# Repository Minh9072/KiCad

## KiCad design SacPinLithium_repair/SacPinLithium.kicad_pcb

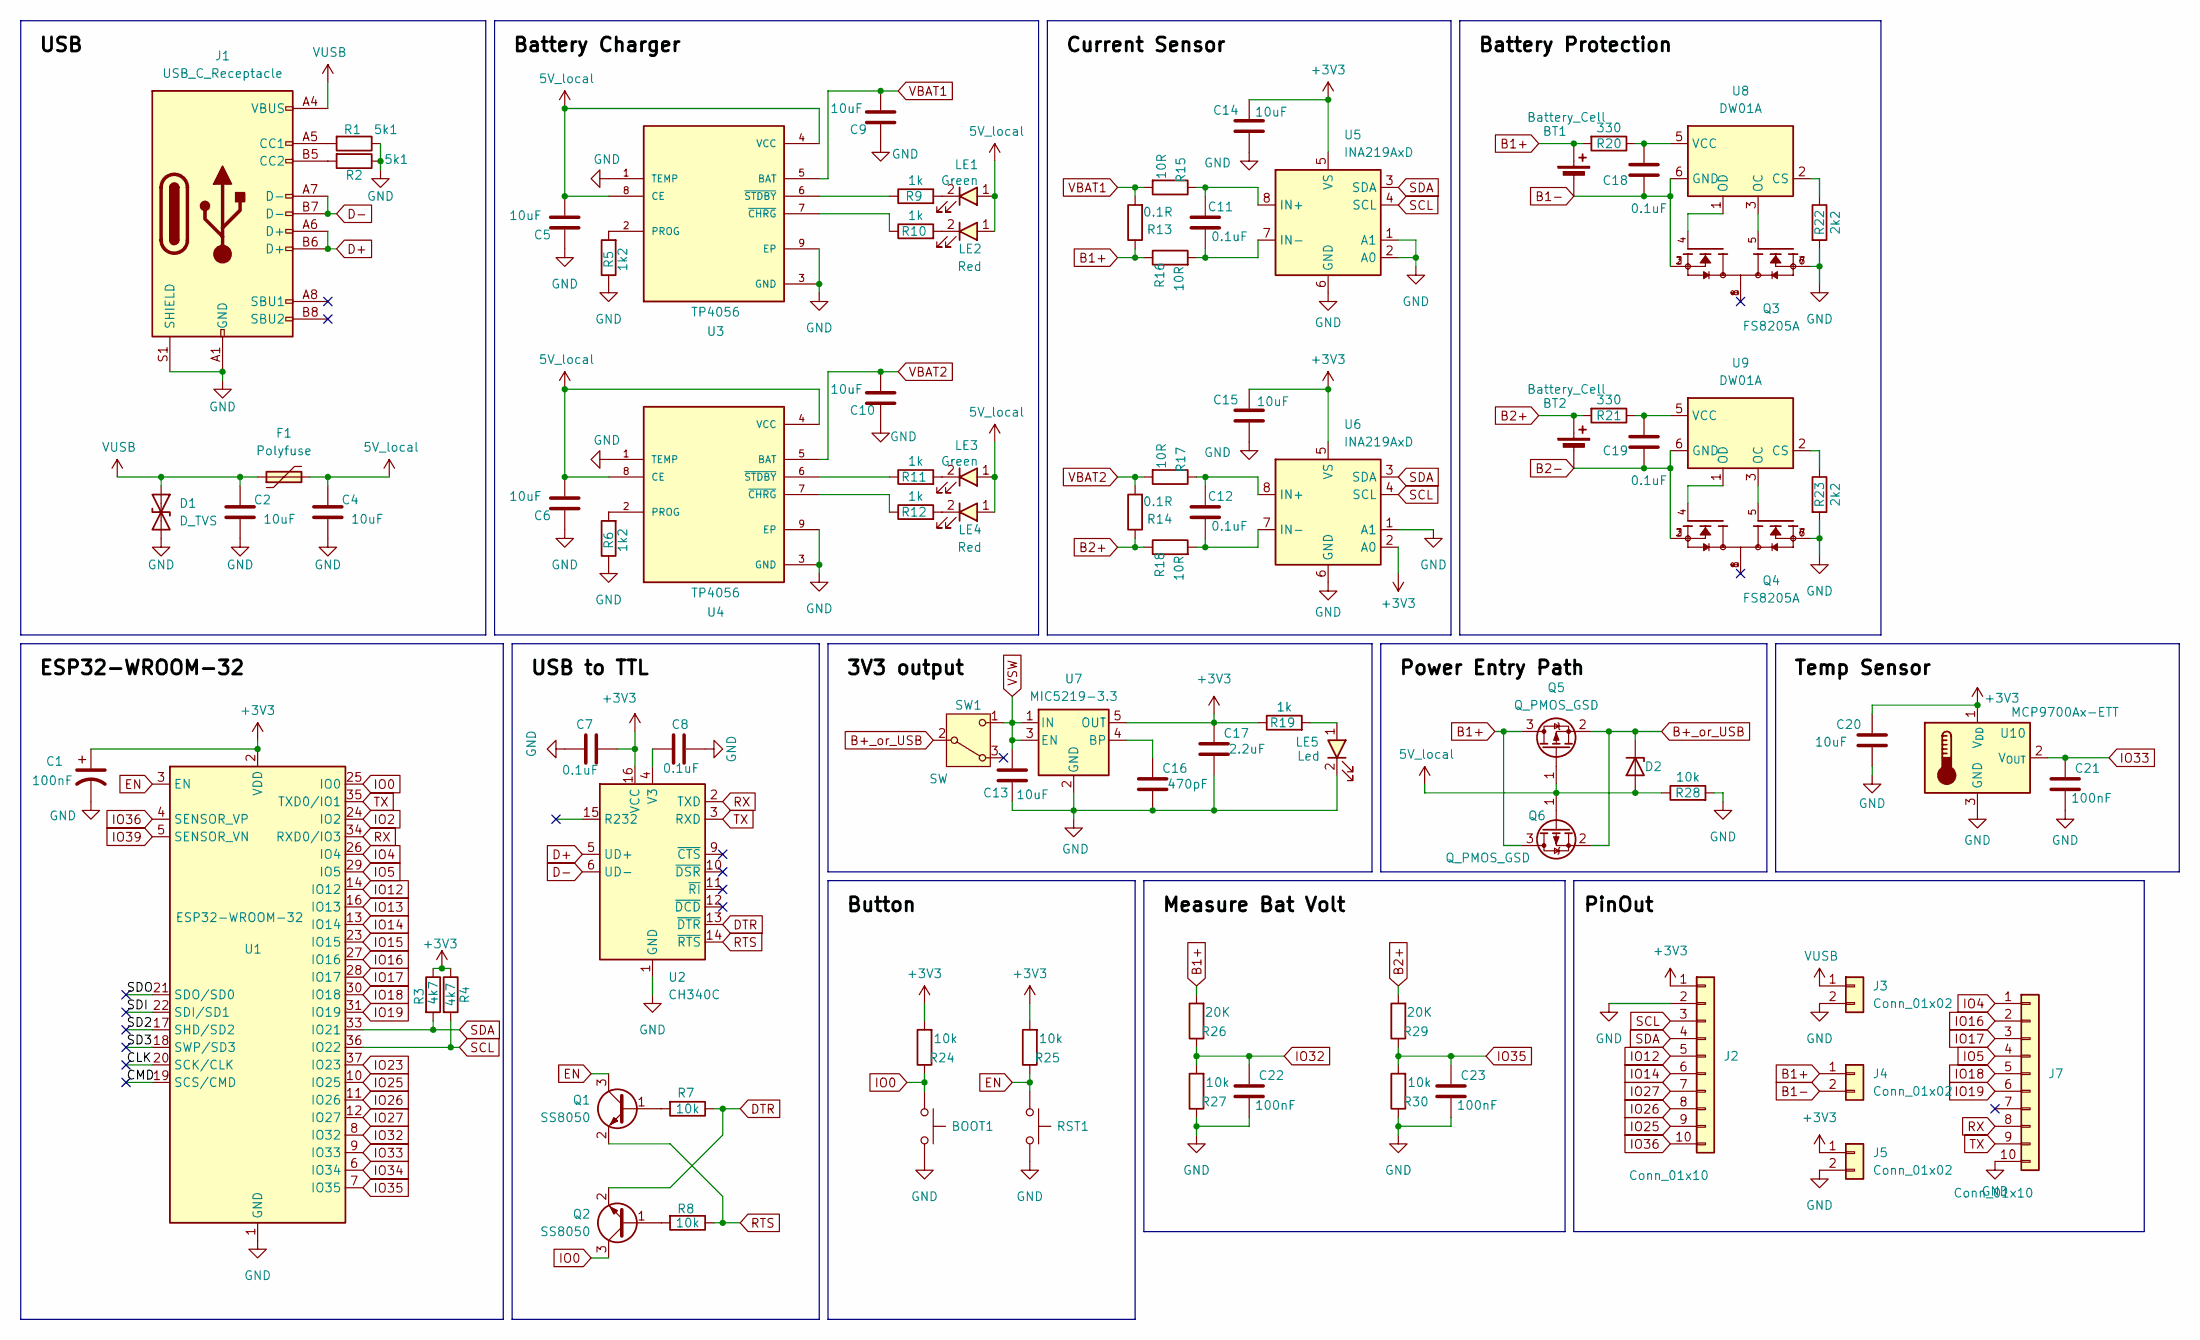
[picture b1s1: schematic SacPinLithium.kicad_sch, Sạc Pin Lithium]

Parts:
BOOT1: SW_Push; SW_Push_SPST_NO_Alps_SKRK
BT1, BT2: Battery_Cell; Minh_BatteryHolder_Keystone_1042_1x18650
C1, C21, C22, C23: 100nF; C_0603
C2, C4, C5, C6, C9, C10, C13, C14, C15, C20: 10uF; C_0603
C7, C8, C11, C12, C18, C19: 0.1uF; C_0603
C16: 470pF; C_0603
C17: 2.2uF; C_0603
D1: D_TVS; Package-Diode-D_SMA
D2: D_SMA
F1: Polyfuse; Fuse_1812_4532Metric
J1: USB_C_Receptacle; USB_C_Receptacle_XKB_U262-16XN-4BVC11
J2, J7: Conn_01x10; PinSocket_1x10_P2.54mm_Vertical
J3, J4, J5: Conn_01x02; PinHeader_1x02_P2.54mm_Vertical
LE1, LE3: Green; L_0603
LE2, LE4: Red; L_0603
LE5: Led; L_0603
Q1, Q2: SS8050; SOT23-3
Q3, Q4: FS8205A; TSSOP-8_4.4x3mm_P0.65mm; PARTREV 1.7
Q5, Q6: Q_PMOS_GSD; SOT23-3
R1, R2: 5k1; R_0805
R3, R4: 4k7; R_0603
R5, R6: 1k2; R_0603
R7, R8, R24, R25, R27, R28, R30: 10k; R_0603
R9, R10, R11, R12, R19: 1k; R_0603
R13, R14: 0.1R; R_2512
R15, R16, R17, R18: 10R; R_0603
R20, R21: 330; R_0603
R22, R23: 2k2; R_0603
R26, R29: 20K; R_0603
RST1: SW_Push; SW_Push_SPST_NO_Alps_SKRK
SW1: SW; SlideSwitch-SS_12F23G4
U1: ESP32-WROOM-32; Minh_ESP32-WROOM-32E
U2: CH340C; SOIC-16_3.9x9.9mm_P1.27mm
U3, U4: TP4056; SOIC-8-1EP_3.9x4.9mm_P1.27mm_EP2.514x3.2mm
U5, U6: INA219AxD; SOIC-8_3.9x4.9mm_P1.27mm
U7: MIC5219-3.3; SOT-23-5
U8, U9: DW01A; SOT-23-6
U10: MCP9700Ax-ETT; SOT23-3

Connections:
5V_local: C4.2, C5.1, C6.1, D2.2 (A), F1.2, LE1.1, LE2.1, LE3.1, LE4.1, Q5.1 (G), Q6.1 (G), R28.1, U3.4 (VCC), U3.8 (CE), U4.4 (VCC), U4.8 (CE); also elsewhere on the board
+3V3: C1.1, C7.1, C14.1, C15.1, C17.1, C20.1, J2.1, J5.1, R3.1, R4.1, R19.1, R24.2, R25.2, U1.2 (VDD), U2.16 (VCC), U5.5 (VS), U6.2 (A0), U6.5 (VS), U7.5 (OUT), U10.1 (V_{DD}); also elsewhere on the board
/CLK: U1.20 (SCK/CLK)
/CMD: U1.19 (SCS/CMD)
/SD2: U1.17 (SHD/SD2)
/SD3: U1.18 (SWP/SD3)
/SDI: U1.22 (SDI/SD1)
/SDO: U1.21 (SDO/SD0)
B1+: BT1.1 (+), J4.1, Q5.3 (D), Q6.3 (D), R13.1, R16.1, R20.2, R26.2; also elsewhere on the board
B1-: BT1.2 (-), C18.2, J4.2, Q3.2, Q3.3, U8.6 (GND); also elsewhere on the board
B2+: BT2.1 (+), R14.1, R18.1, R21.2, R29.2
B2-: BT2.2 (-), C19.2, Q4.2, Q4.3, U9.6 (GND)
B+_or_USB: D2.1 (K), Q5.2 (S), Q6.2 (S), SW1.2 (B)
D+: J1.A6 (D+), J1.B6 (D+), U2.5 (UD+)
D-: J1.A7 (D-), J1.B7 (D-), U2.6 (UD-)
DTR: Q2.2 (E), R7.1, U2.13 (~DTR)
EN: Q1.3 (C), R25.1, RST1.1, U1.3 (EN)
GND: BOOT1.2, C1.2, C2.1, C4.1, C5.2, C6.2, C7.2, C8.2, C9.2, C10.2, C13.2, C14.2, C15.2, C16.2, C17.2, C20.2, C21.2, C22.2, C23.2, D1.2 (A2), J1.A1 (GND), J1.A12 (GND), J1.B1 (GND), J1.B12 (GND), J1.S1 (SHIELD), J2.2, J3.2, J5.2, J7.10, LE5.2, Q3.6, Q3.7, Q4.6, Q4.7, R1.1, R2.1, R5.1, R6.1, R22.2, R23.2, R27.1, R28.2, R30.1, RST1.2, U1.1 (GND), U1.15 (GND), U1.38 (GND), U1.39 (GND), U2.1 (GND), U3.1 (TEMP), U3.3 (GND), U3.9 (EP), U4.1 (TEMP), U4.3 (GND), U4.9 (EP), U5.1 (A1), U5.2 (A0), U5.6 (GND), U6.1 (A1), U6.6 (GND), U7.2 (GND), U10.3 (GND); also elsewhere on the board
IO0: BOOT1.1, Q2.3 (C), R24.1, U1.25 (IO0)
IO2: U1.24 (IO2)
IO4: J7.1, U1.26 (IO4)
IO5: J7.4, U1.29 (IO5)
IO12: J2.5, U1.14 (IO12)
IO13: U1.16 (IO13)
IO14: J2.6, U1.13 (IO14)
IO15: U1.23 (IO15)
IO16: J7.2, U1.27 (IO16)
IO17: J7.3, U1.28 (IO17)
IO18: J7.5, U1.30 (IO18)
IO19: J7.6, U1.31 (IO19)
IO23: U1.37 (IO23)
IO25: J2.9, U1.10 (IO25)
IO26: J2.8, U1.11 (IO26)
IO27: J2.7, U1.12 (IO27)
IO32: C22.1, R26.1, R27.2, U1.8 (IO32)
IO33: C21.1, U1.9 (IO33), U10.2 (V_{OUT})
IO34: U1.6 (IO34)
IO35: C23.1, R29.1, R30.2, U1.7 (IO35)
IO36: J2.10, U1.4 (SENSOR_VP)
IO39: U1.5 (SENSOR_VN)
unnamed: J1.A5 (CC1), R1.2
unnamed: J1.B5 (CC2), R2.2
unnamed 42: LE1.2, R9.2; also elsewhere on the board
unnamed 43: LE2.2, R10.2; also elsewhere on the board
unnamed 44: LE3.2, R11.2; also elsewhere on the board
unnamed 45: LE4.2, R12.2; also elsewhere on the board
unnamed: LE5.1, R19.2
unnamed: Q1.1 (B), R7.2
unnamed: Q2.1 (B), R8.2
unnamed: C8.1, U2.4 (V3)
unnamed: R5.2, U3.2 (PROG)
unnamed: R10.1, U3.7 (~CHRG)
unnamed: R9.1, U3.6 (~STDBY)
unnamed: R6.2, U4.2 (PROG)
unnamed: R12.1, U4.7 (~CHRG)
unnamed: R11.1, U4.6 (~STDBY)
unnamed: C11.1, R15.1, U5.8 (IN+)
unnamed: C11.2, R16.2, U5.7 (IN-)
unnamed: C12.1, R17.1, U6.8 (IN+)
unnamed: C12.2, R18.2, U6.7 (IN-)
unnamed: C16.1, U7.4 (BP)
unnamed: R22.1, U8.2 (CS)
unnamed: Q3.5, U8.3 (OC)
unnamed: Q3.4, U8.1 (OD)
unnamed: C18.1, R20.1, U8.5 (VCC)
unnamed: R23.1, U9.2 (CS)
unnamed: Q4.5, U9.3 (OC)
unnamed: Q4.4, U9.1 (OD)
unnamed: C19.1, R21.1, U9.5 (VCC)
RTS: Q1.2 (E), R8.1, U2.14 (~RTS)
RX: J7.8, U1.34 (RXD0/IO3), U2.2 (TXD)
SCL: J2.3, R4.2, U1.36 (IO22), U5.4 (SCL), U6.4 (SCL)
SDA: J2.4, R3.2, U1.33 (IO21), U5.3 (SDA), U6.3 (SDA)
TX: J7.9, U1.35 (TXD0/IO1), U2.3 (RXD)
VBAT1: C9.1, R13.2, R15.2, U3.5 (BAT)
VBAT2: C10.1, R14.2, R17.2, U4.5 (BAT)
VSW: C13.1, SW1.1 (C), U7.1 (IN), U7.3 (EN)
VUSB: C2.2, D1.1 (A1), F1.1, J1.A4 (VBUS), J1.A9 (VBUS), J1.B4 (VBUS), J1.B9 (VBUS), J3.1; also elsewhere on the board

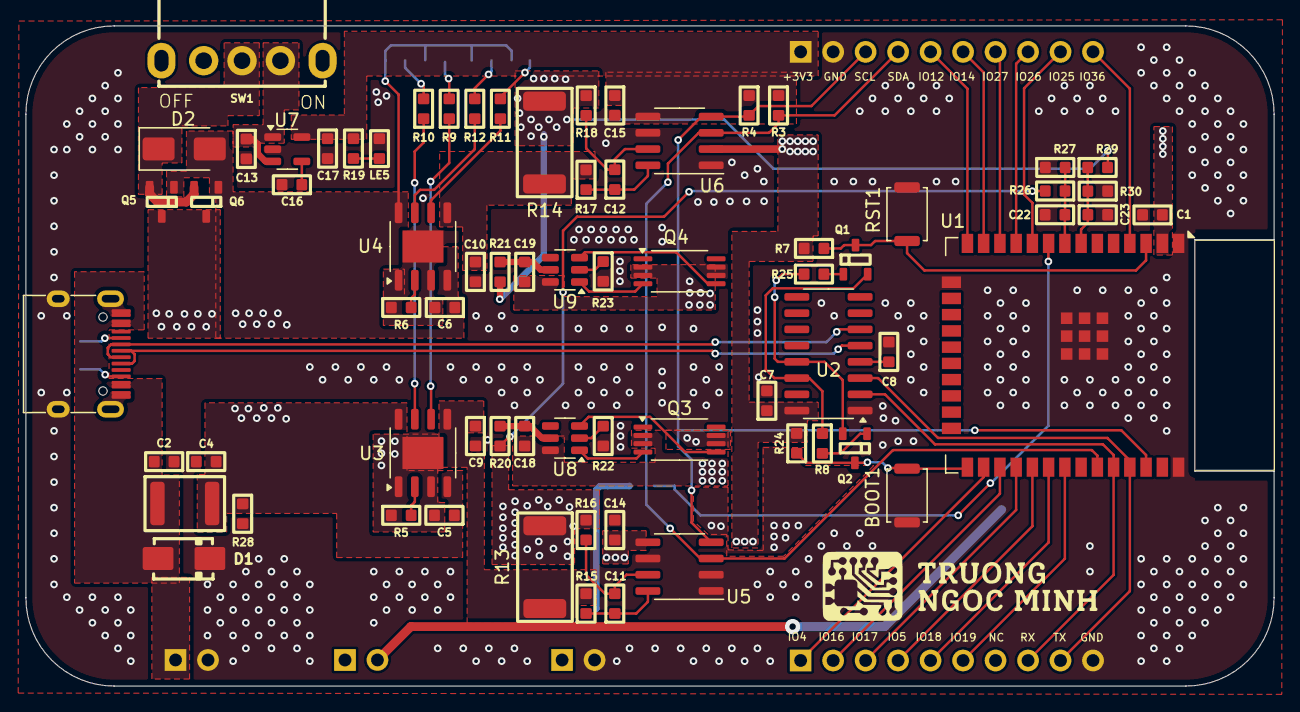
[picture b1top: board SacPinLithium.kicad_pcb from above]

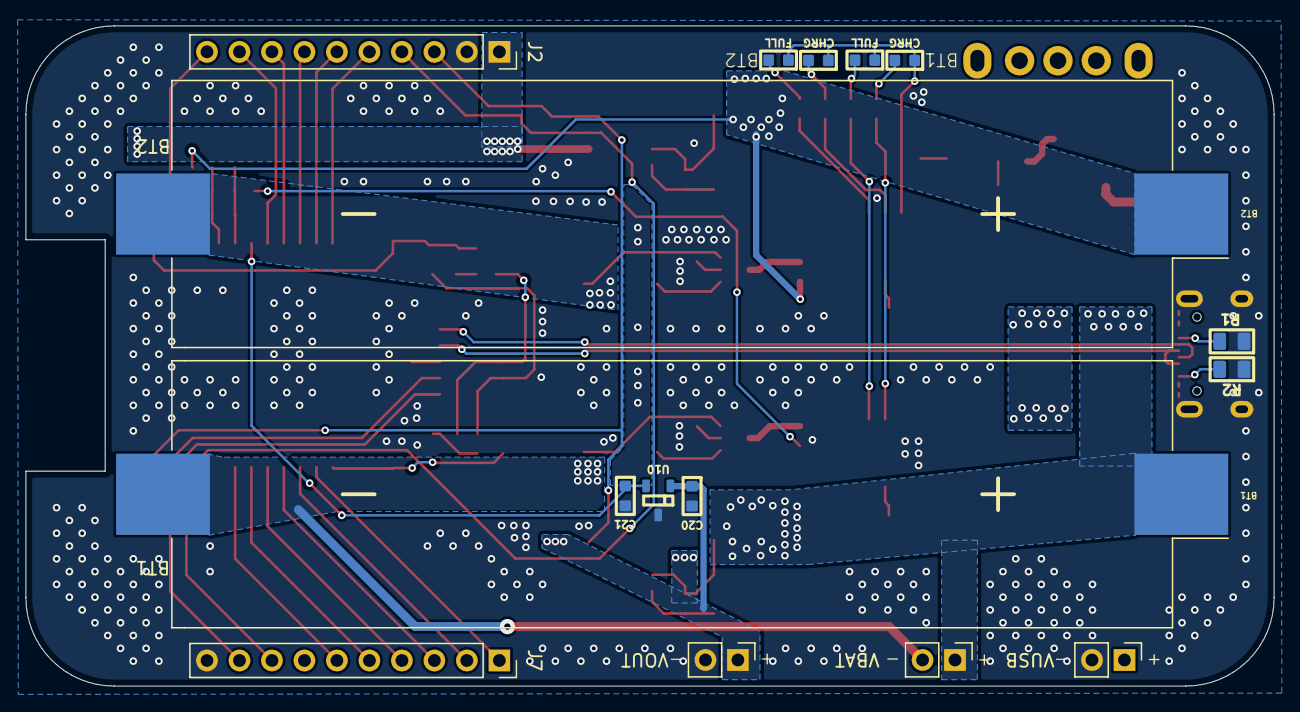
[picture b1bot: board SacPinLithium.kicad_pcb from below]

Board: 2 copper layers, 97.6 x 51.6 mm, 87 parts (16 on the bottom side), 66 nets.

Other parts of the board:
CHRG: Red; L_0603
CHRG#2: Red; L_0603
FULL: Green; L_0603
FULL#2: Green; L_0603
VBAT: Conn_01x02; PinHeader_1x02_P2.54mm_Vertical
VOUT: Conn_01x02; PinHeader_1x02_P2.54mm_Vertical
VUSB: Conn_01x02; PinHeader_1x02_P2.54mm_Vertical

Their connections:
5V_local: CHRG.1, CHRG#2.1, FULL.1, FULL#2.1; also elsewhere on the board
+3V3: VOUT.1; also elsewhere on the board
B1+: VBAT.1; also elsewhere on the board
B1-: VBAT.2; also elsewhere on the board
GND: VOUT.2, VUSB.2; also elsewhere on the board
unnamed 42: FULL.2; also elsewhere on the board
unnamed 43: CHRG#2.2; also elsewhere on the board
unnamed 44: FULL#2.2; also elsewhere on the board
unnamed 45: CHRG.2; also elsewhere on the board
VUSB: VUSB.1; also elsewhere on the board

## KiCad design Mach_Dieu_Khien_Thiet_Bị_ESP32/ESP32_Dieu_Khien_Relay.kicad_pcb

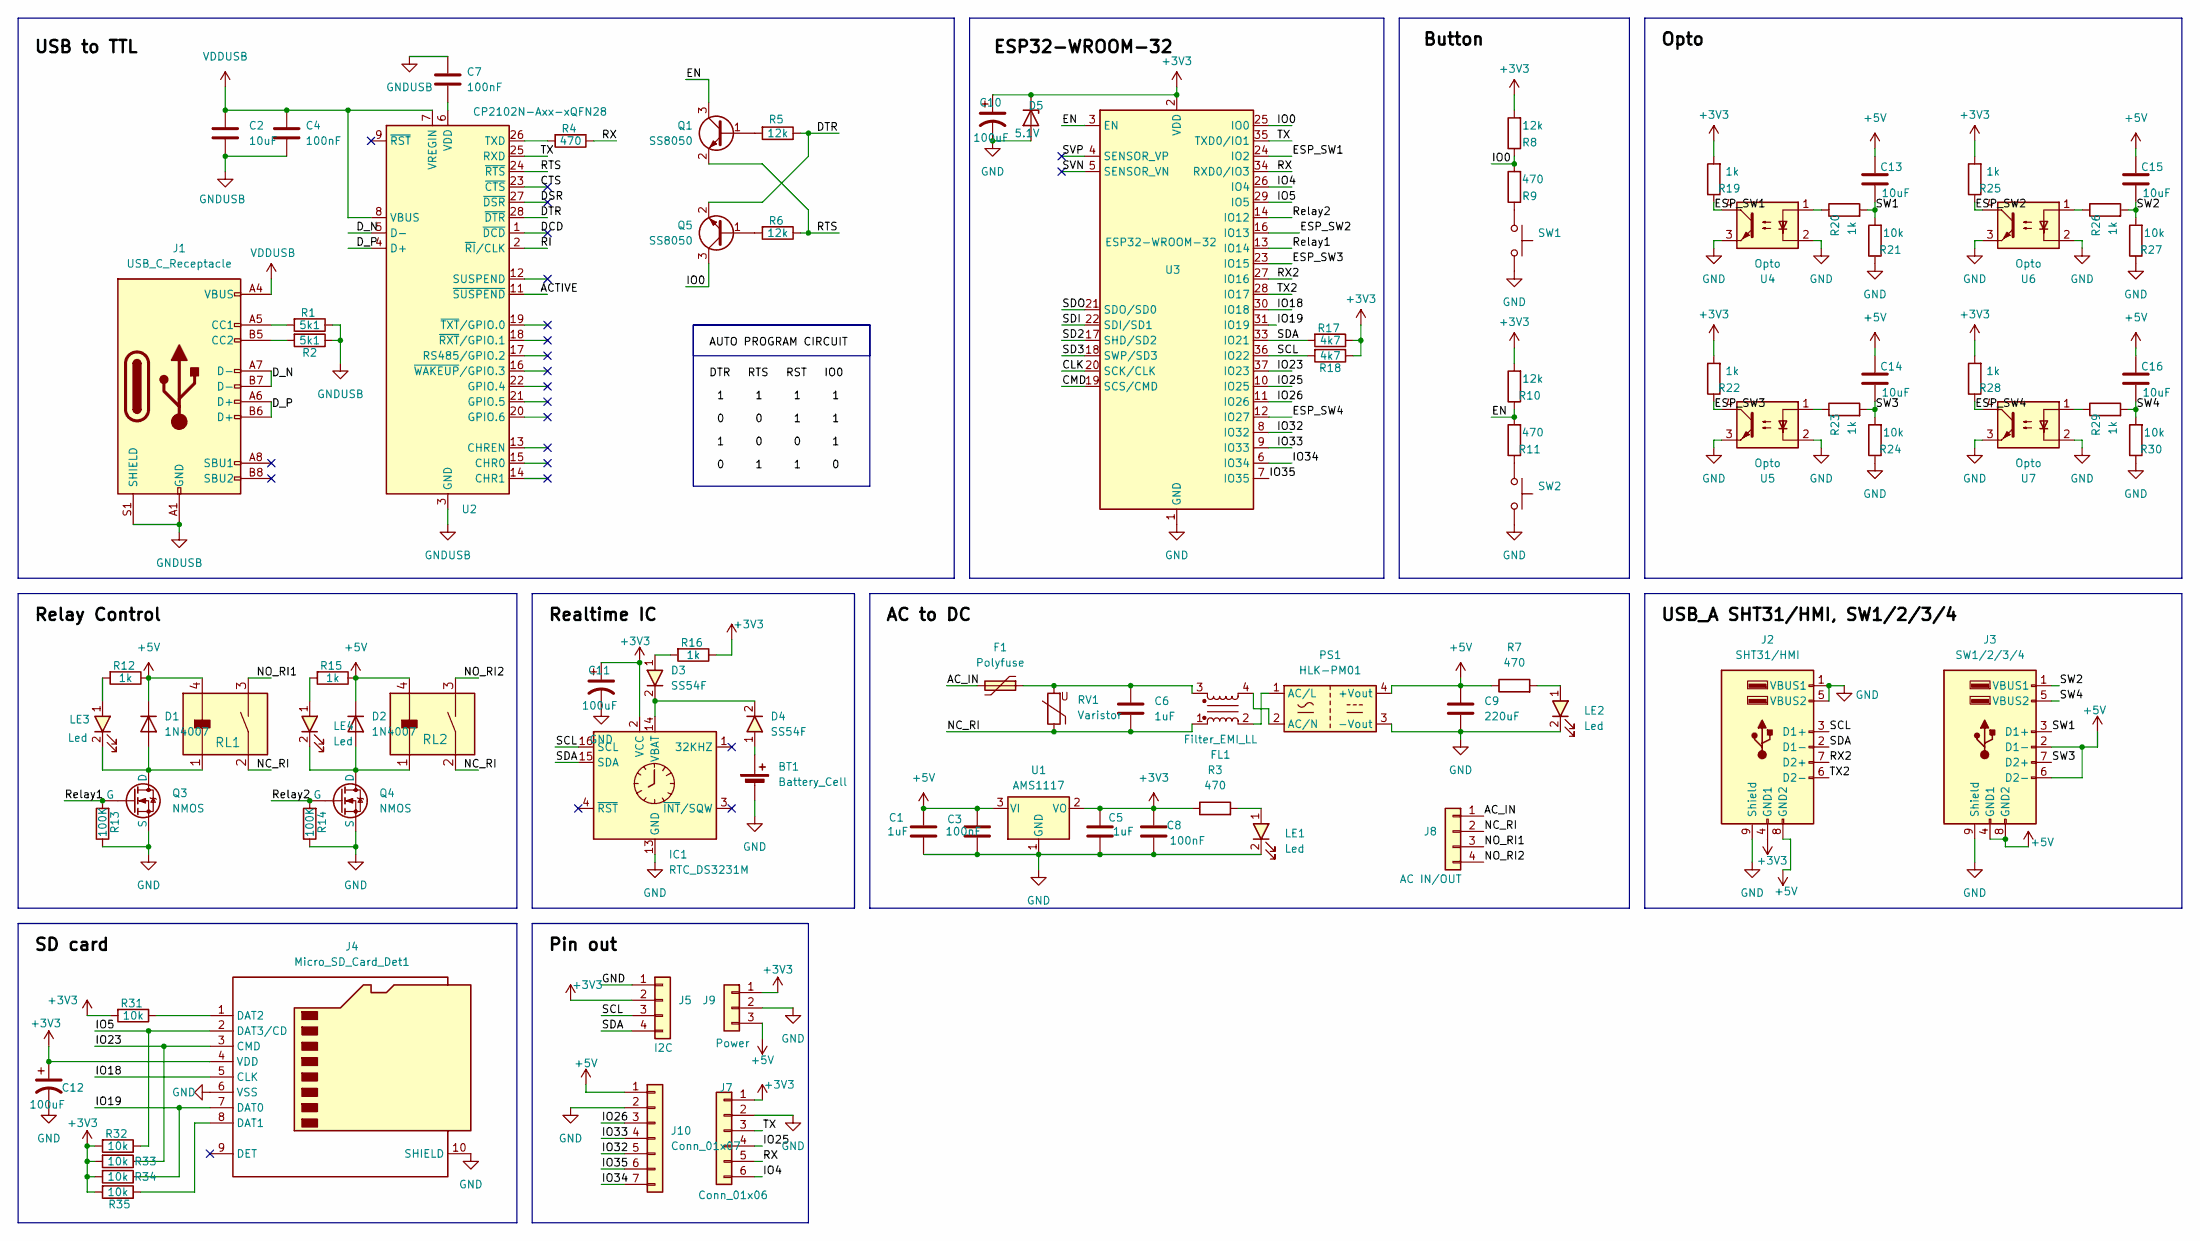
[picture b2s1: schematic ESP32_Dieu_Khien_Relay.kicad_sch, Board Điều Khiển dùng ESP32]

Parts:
BT1: Battery_Cell; BatteryHolder-SMD-CR1220
C1, C5: 1uF; C_0603
C2, C13, C14, C15, C16: 10uF; C_0603
C3, C4, C7, C8: 100nF; C_0603
C6: 1uF; C-Polyester-Rect-L16.5mm-W5.0mm-P15.00mm-MKT
C9: 220uF; CP_Elec_5x3
C10, C11, C12: 100uF; C_0603
D1, D2: 1N4007; Package-Diode-D_SMA
D3, D4: SS54F; Package-Diode-D_SMA
D5: 5.1V; Package-Diode-D_SOD_123
F1: Polyfuse; Fuse_Littelfuse_395Series
FL1: Filter_EMI_LL; ACFilterChoke-UU9.8
IC1: RTC_DS3231M; SOIC-16W_7.5x10.3mm_P1.27mm
J1: USB_C_Receptacle; USB_C_Receptacle_XKB_U262-16XN-4BVC11
J2: SHT31/HMI; USB_A_CUI_UJ2-ADH-TH_Horizontal_Stacked
J3: SW1/2/3/4; USB_A_CUI_UJ2-ADH-TH_Horizontal_Stacked
J4: Micro_SD_Card_Det1; Socket_MicroSD-9P
J5: I2C; PinHeader_1x04_P2.54mm_Vertical
J7: Conn_01x06; PinHeader_1x06_P2.54mm_Vertical
J8: AC IN/OUT; TerminalBlock-Vert-THT-8P-P9.5mm-Screw_HB9500
J9: Power; PinHeader_1x03_P2.54mm_Vertical
J10: Conn_01x07; PinHeader_1x07_P2.54mm_Vertical
LE1, LE2, LE3, LE4: Led; L_0603
PS1: HLK-PM01; PowerSuppy-ACDC-HLK_P01
Q1, Q5: SS8050; SOT-23
Q3, Q4: NMOS; SOT23-3
R1, R2: 5k1; R_0603
R3, R4, R7, R9, R11: 470; R_0603
R5, R6, R8, R10: 12k; R_0603
R12, R15, R16, R19, R20, R22, R23, R25, R26, R28, R29: 1k; R_0603
R13, R14: 100K; R_0603
R17, R18: 4k7; R_0603
R21, R24, R27, R30, R31, R32, R33, R34, R35: 10k; R_0603
RL1, RL2: Relay_G5NB-1A-E_DC5; Relay-G5NB_1A_E_DC5
RV1: Varistor; Varistor-RV-Disc-D12mm-W3.9mm-P7.5mm
SW1, SW2: SW_Push; SW_Push_SPST_NO_Alps_SKRK
U1: AMS1117; SOT233
U2: CP2102N-Axx-xQFN28; QFN-28-1EP_5x5mm_P0.5mm_EP3.35x3.35mm
U3: ESP32-WROOM-32
U4, U5, U6, U7: Opto; OptoIsolation-EL357N-G

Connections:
+3V3: C5.1, C8.1, C10.1, C11.1, C12.1, D5.1 (K), IC1.2 (VCC), J2.4 (GND1), J4.4 (VDD), J5.2, J7.1, J9.1, R3.1, R8.2, R10.2, R16.1, R17.1, R18.1, R19.2, R22.2, R25.2, R28.2, R31.2, R32.2, R33.2, R34.2, R35.2, U1.2 (VO), U3.2 (VDD); also elsewhere on the board
+5V: C1.1, C3.1, C9.1, C13.1, C14.1, C15.1, C16.1, D1.1 (K), D2.1 (K), J2.8 (GND2), J3.2 (D1-), J3.4 (GND1), J3.6 (D2-), J3.8 (GND2), J9.3, J10.1, PS1.4 (+Vout), R7.1, R12.1, R15.1, RL1.4, RL2.4, U1.3 (VI); also elsewhere on the board
/ACTIVE: U2.11 (~SUSPEND)
/AC_IN: F1.2, J8.1
/CLK: U3.20 (SCK/CLK)
/CMD: U3.19 (SCS/CMD)
/CTS: U2.23 (~CTS)
/DCD: U2.1 (~DCD)
/DSR: U2.27 (~DSR)
/DTR: Q5.2 (E), R5.1, U2.28 (~DTR)
/D_N: J1.A7 (D-), J1.B7 (D-), U2.5 (D-)
/D_P: J1.A6 (D+), J1.B6 (D+), U2.4 (D+)
/EN: Q1.3 (C), R10.1, R11.2, U3.3 (EN)
/ESP_SW1: R19.1, U3.24 (IO2), U4.4
/ESP_SW2: R25.1, U3.16 (IO13), U6.4
/ESP_SW3: R22.1, U3.23 (IO15), U5.4
/ESP_SW4: R28.1, U3.12 (IO27), U7.4
/IO0: Q5.3 (C), R8.1, R9.2, U3.25 (IO0)
/IO4: J7.6, U3.26 (IO4)
/IO5: J4.2 (DAT3/CD), R32.1, U3.29 (IO5)
/IO18: J4.5 (CLK), U3.30 (IO18)
/IO19: J4.7 (DAT0), R34.1, U3.31 (IO19)
/IO23: J4.3 (CMD), R33.1, U3.37 (IO23)
/IO25: J7.4, U3.10 (IO25)
/IO26: J10.3, U3.11 (IO26); also elsewhere on the board
/IO32: J10.5, U3.8 (IO32); also elsewhere on the board
/IO33: J10.4, U3.9 (IO33); also elsewhere on the board
/IO34: J10.7, U3.6 (IO34); also elsewhere on the board
/IO35: J10.6, U3.7 (IO35); also elsewhere on the board
/NC_RI: C6.2, FL1.1, J8.2, RL1.2, RL2.2, RV1.1
/NO_RI1: J8.3, RL1.3
/NO_RI2: J8.4, RL2.3
/RI: U2.2 (~RI/CLK)
/RTS: Q1.2 (E), R6.1, U2.24 (~RTS)
/RX: J7.5, R4.1, U3.34 (RXD0/IO3)
/RX2: J2.7 (D2+), U3.27 (IO16)
/Relay1: Q3.1 (G), R13.2, U3.13 (IO14)
/Relay2: Q4.1 (G), R14.2, U3.14 (IO12)
/SCL: IC1.16 (SCL), J2.3 (D1+), J5.3, R18.2, U3.36 (IO22); also elsewhere on the board
/SD2: U3.17 (SHD/SD2)
/SD3: U3.18 (SWP/SD3)
/SDA: IC1.15 (SDA), J2.2 (D1-), J5.4, R17.2, U3.33 (IO21); also elsewhere on the board
/SDI: U3.22 (SDI/SD1)
/SDO: U3.21 (SDO/SD0)
/SVN: U3.5 (SENSOR_VN)
/SVP: U3.4 (SENSOR_VP)
/SW1: C13.2, J3.3 (D1+), R20.2, R21.2
/SW2: C15.2, J3.1 (VBUS1), R26.2, R27.2
/SW3: C14.2, J3.7 (D2+), R23.2, R24.2
/SW4: C16.2, J3.5 (VBUS2), R29.2, R30.2
/TX: J7.3, U2.25 (RXD), U3.35 (TXD0/IO1)
/TX2: J2.6 (D2-), U3.28 (IO17)
GND: BT1.2 (-), C1.2, C3.2, C5.2, C8.2, C9.2, C10.2, C11.2, C12.2, D5.2 (A), IC1.5 (GND), IC1.6 (GND), IC1.7 (GND), IC1.8 (GND), IC1.9 (GND), IC1.10 (GND), IC1.11 (GND), IC1.12 (GND), IC1.13 (GND), J2.1 (VBUS1), J2.5 (VBUS2), J2.9 (Shield), J3.9 (Shield), J4.6 (VSS), J4.10 (SHIELD), J7.2, J9.2, J10.2, LE1.2, LE2.2, PS1.3 (-Vout), Q3.2 (S), Q4.2 (S), R13.1, R14.1, R21.1, R24.1, R27.1, R30.1, SW1.2, SW2.2, U1.1 (GND), U3.1 (GND), U3.15 (GND), U3.38 (GND), U3.39 (GND), U4.2, U4.3, U5.2, U5.3, U6.2, U6.3, U7.2, U7.3; also elsewhere on the board
GNDUSB: C2.2, C4.2, C7.1, J1.A1 (GND), J1.A12 (GND), J1.B1 (GND), J1.B12 (GND), J1.S1 (SHIELD), R1.1, R2.1, U2.3 (GND), U2.29 (GND)
unnamed: BT1.1 (+), D4.1
unnamed: C6.1, F1.1, FL1.3, RV1.2
unnamed 56: D1.2 (A), LE3.2, Q3.3 (D), RL1.1; also elsewhere on the board
unnamed 57: D2.2 (A), LE4.2, Q4.3 (D), RL2.1; also elsewhere on the board
unnamed: D3.1, R16.2
unnamed: D3.2, D4.2, IC1.14 (VBAT)
unnamed: J1.A5 (CC1), R1.2
unnamed: J1.B5 (CC2), R2.2
unnamed: J4.8 (DAT1), R35.1
unnamed: J4.1 (DAT2), R31.1
unnamed 64: LE1.1, R3.2; also elsewhere on the board
unnamed 65: LE2.1, R7.2; also elsewhere on the board
unnamed 66: LE3.1, R12.2; also elsewhere on the board
unnamed 67: LE4.1, R15.2; also elsewhere on the board
unnamed: FL1.2, PS1.1 (AC/L)
unnamed: FL1.4, PS1.2 (AC/N)
unnamed: Q1.1 (B), R5.2
unnamed: Q5.1 (B), R6.2
unnamed 72: R9.1, SW1.1; also elsewhere on the board
unnamed 73: R11.1, SW2.1; also elsewhere on the board
unnamed: R20.1, U4.1
unnamed: R23.1, U5.1
unnamed: R26.1, U6.1
unnamed: R29.1, U7.1
unnamed: R4.2, U2.26 (TXD)
unnamed: C7.2, U2.6 (VDD)
VDDUSB: C2.1, C4.1, J1.A4 (VBUS), J1.A9 (VBUS), J1.B4 (VBUS), J1.B9 (VBUS), U2.7 (VREGIN), U2.8 (VBUS)

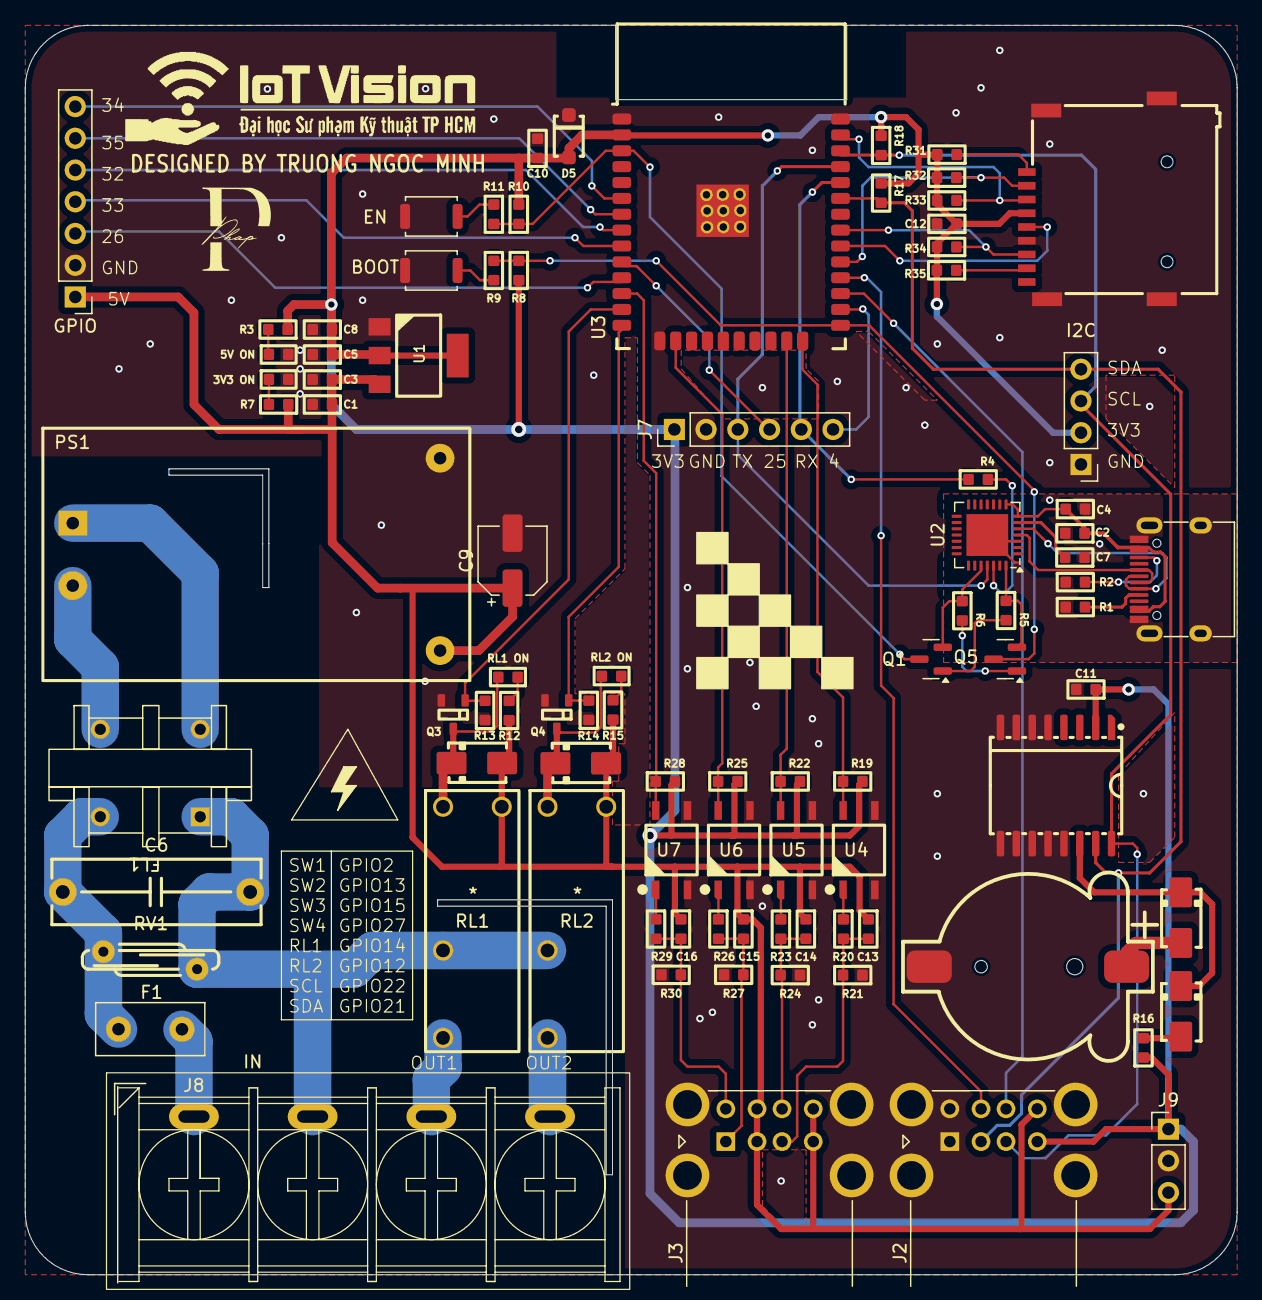
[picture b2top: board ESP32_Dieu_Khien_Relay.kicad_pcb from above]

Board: 2 copper layers, 97.0 x 100.0 mm, 90 parts (0 on the bottom side), 68 nets.

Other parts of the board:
3V3 ON, 5V ON: Led; L_0603
BOOT: SW_Push; SW_Push_SPST_NO_Alps_SKRK
EN: SW_Push; SW_Push_SPST_NO_Alps_SKRK
GPIO: Conn_01x07; PinHeader_1x07_P2.54mm_Vertical
I2C: I2C; PinHeader_1x04_P2.54mm_Vertical
RL1 ON, RL2 ON: Led; L_0603

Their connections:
+3V3: I2C.2; also elsewhere on the board
+5V: GPIO.1; also elsewhere on the board
/IO26: GPIO.3; also elsewhere on the board
/IO32: GPIO.5; also elsewhere on the board
/IO33: GPIO.4; also elsewhere on the board
/IO34: GPIO.7; also elsewhere on the board
/IO35: GPIO.6; also elsewhere on the board
/SCL: I2C.3; also elsewhere on the board
/SDA: I2C.4; also elsewhere on the board
GND: 3V3 ON.2, 5V ON.2, BOOT.2, EN.2, GPIO.2, I2C.1; also elsewhere on the board
unnamed 56: RL1 ON.2; also elsewhere on the board
unnamed 57: RL2 ON.2; also elsewhere on the board
unnamed 64: 5V ON.1; also elsewhere on the board
unnamed 65: 3V3 ON.1; also elsewhere on the board
unnamed 66: RL1 ON.1; also elsewhere on the board
unnamed 67: RL2 ON.1; also elsewhere on the board
unnamed 72: BOOT.1; also elsewhere on the board
unnamed 73: EN.1; also elsewhere on the board

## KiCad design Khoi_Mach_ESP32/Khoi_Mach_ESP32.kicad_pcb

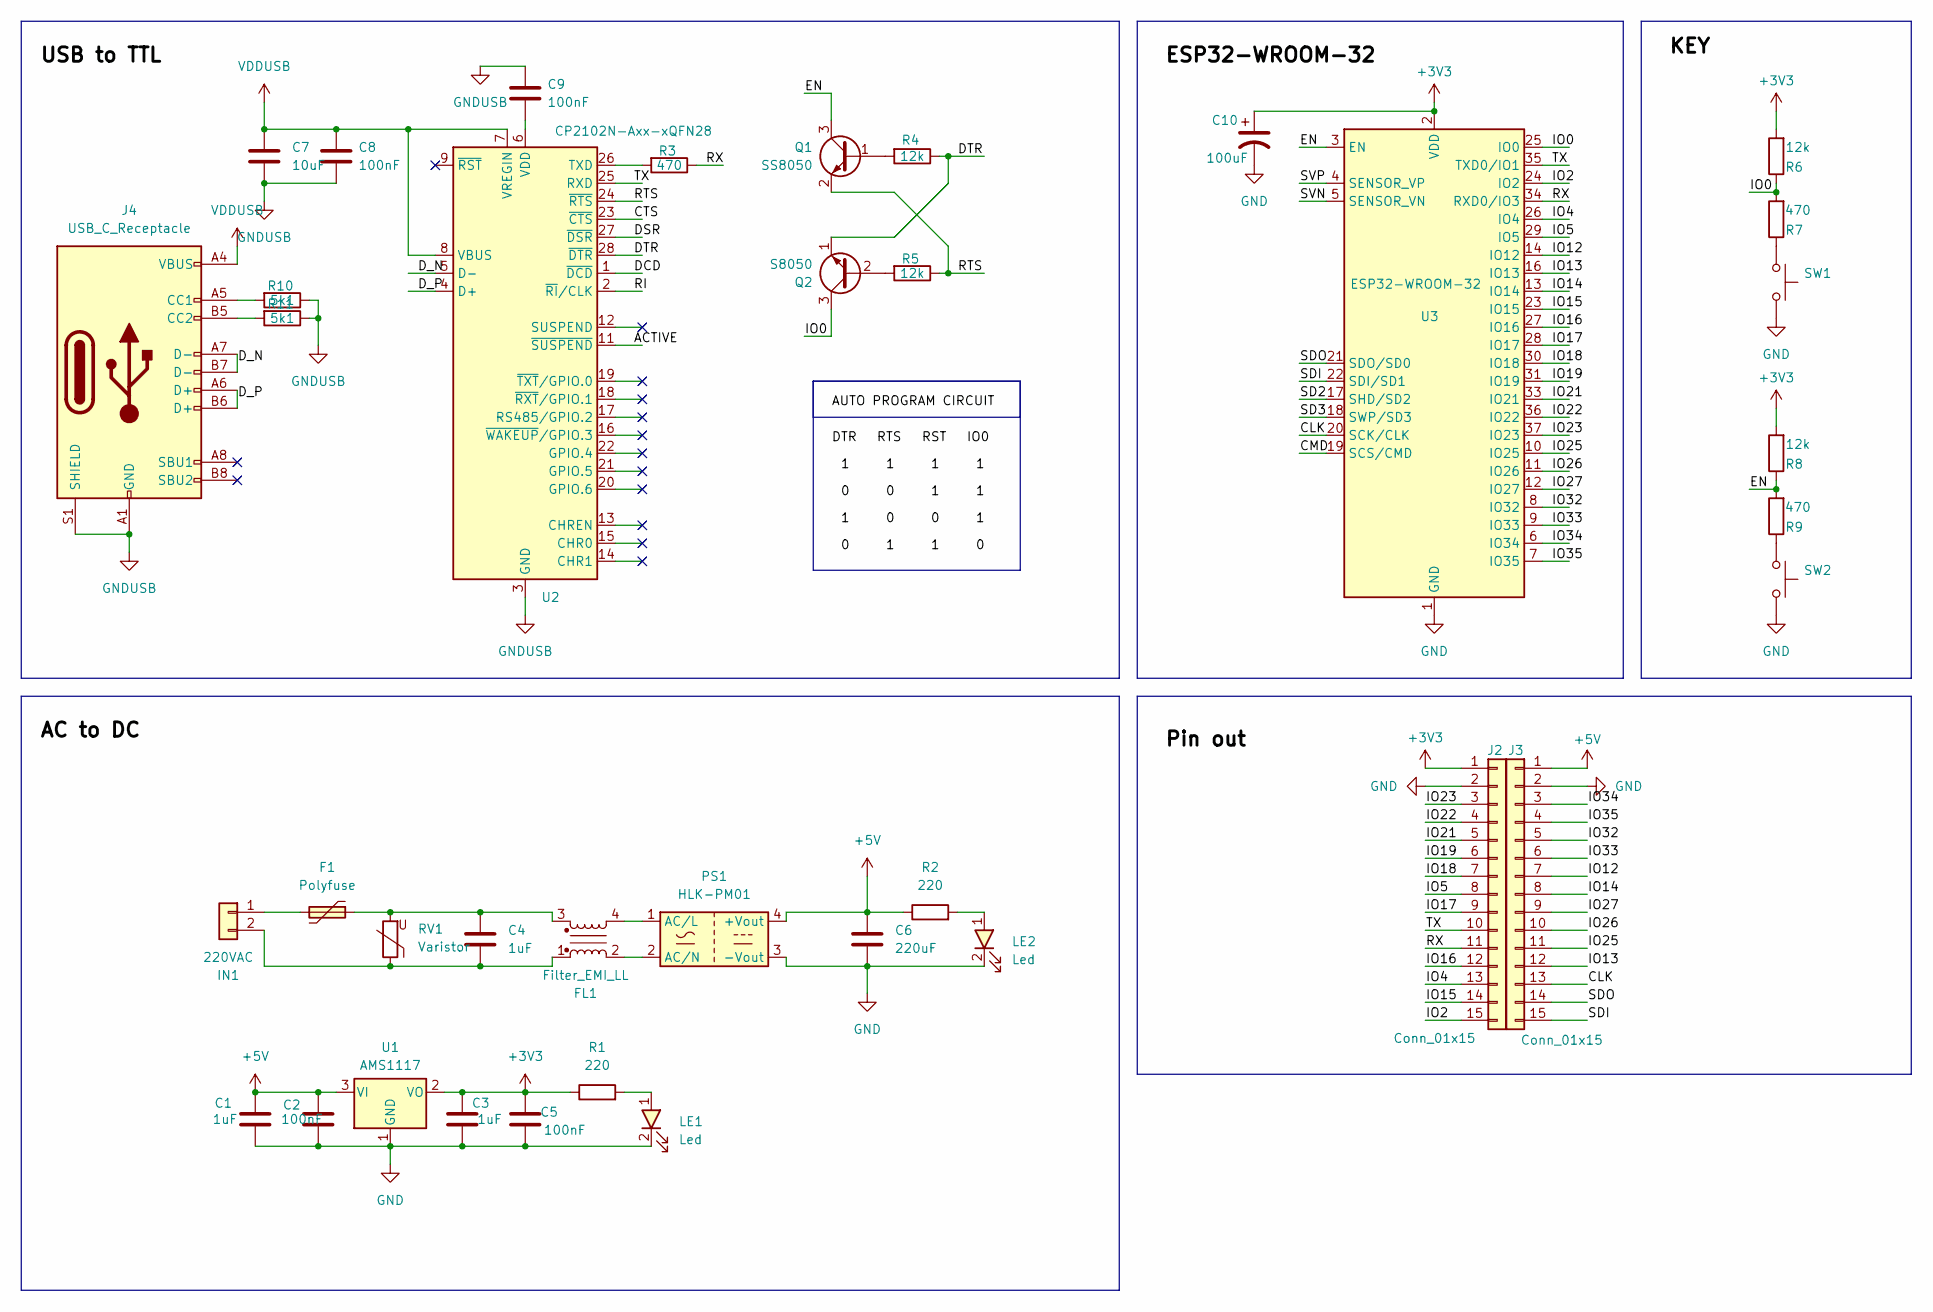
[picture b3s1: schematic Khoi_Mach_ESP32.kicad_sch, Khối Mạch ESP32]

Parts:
C1, C3: 1uF; C_0603
C2, C5, C8, C9: 100nF; C_0603
C4: 1uF; C-Polyester-Rect-L16.5mm-W5.0mm-P15.00mm-MKT
C6: 220uF; CP_Elec_5x3
C7: 10uF; C_0603
C10: 100uF; C_0603
F1: Polyfuse; Fuse_Littelfuse_395Series
FL1: Filter_EMI_LL; ACFilterChoke-UU9.8
IN1: 220VAC; TerminalBlock-Vert-THT-2P-5.08mm-KF5.08
J2, J3: Conn_01x15; PinHeader_1x15_P2.54mm_Vertical
J4: USB_C_Receptacle; USB_C_Receptacle_XKB_U262-16XN-4BVC11
LE1, LE2: Led; L_0603
PS1: HLK-PM01; PowerSuppy-ACDC-HLK_P01
Q1: SS8050; SOT-23
Q2: S8050; SOT-23
R1, R2: 220; R_0603
R3, R7, R9: 470; R_0603
R4, R5, R6, R8: 12k; R_0603
R10, R11: 5k1; R_0603
RV1: Varistor; Varistor-RV-Disc-D12mm-W3.9mm-P7.5mm
SW1, SW2: SW_Push; SW_Push_SPST_NO_Alps_SKRK
U1: AMS1117; SOT233
U2: CP2102N-Axx-xQFN28; QFN-28-1EP_5x5mm_P0.5mm_EP3.35x3.35mm
U3: ESP32-WROOM-32

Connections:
+3V3: C3.1, C5.1, C10.1, J2.1, R1.1, R6.2, R8.2, U1.2 (VO), U3.2 (VDD)
+5V: C1.1, C2.1, C6.1, J3.1, PS1.4 (+Vout), R2.1, U1.3 (VI)
/ACTIVE: U2.11 (~SUSPEND)
/CLK: J3.13, U3.20 (SCK/CLK)
/CMD: U3.19 (SCS/CMD)
/CTS: U2.23 (~CTS)
/DCD: U2.1 (~DCD)
/DSR: U2.27 (~DSR)
/DTR: Q2.1 (E), R4.1, U2.28 (~DTR)
/D_N: J4.A7 (D-), J4.B7 (D-), U2.5 (D-)
/D_P: J4.A6 (D+), J4.B6 (D+), U2.4 (D+)
/EN: Q1.3 (C), R8.1, R9.2, U3.3 (EN)
/IO0: Q2.3 (C), R6.1, R7.2, U3.25 (IO0)
/IO2: J2.15, U3.24 (IO2)
/IO4: J2.13, U3.26 (IO4)
/IO5: J2.8, U3.29 (IO5)
/IO12: J3.7, U3.14 (IO12)
/IO13: J3.12, U3.16 (IO13)
/IO14: J3.8, U3.13 (IO14)
/IO15: J2.14, U3.23 (IO15)
/IO16: J2.12, U3.27 (IO16)
/IO17: J2.9, U3.28 (IO17)
/IO18: J2.7, U3.30 (IO18)
/IO19: J2.6, U3.31 (IO19)
/IO21: J2.5, U3.33 (IO21)
/IO22: J2.4, U3.36 (IO22)
/IO23: J2.3, U3.37 (IO23)
/IO25: J3.11, U3.10 (IO25)
/IO26: J3.10, U3.11 (IO26)
/IO27: J3.9, U3.12 (IO27)
/IO32: J3.5, U3.8 (IO32)
/IO33: J3.6, U3.9 (IO33)
/IO34: J3.3, U3.6 (IO34)
/IO35: J3.4, U3.7 (IO35)
/RI: U2.2 (~RI/CLK)
/RTS: Q1.2 (E), R5.1, U2.24 (~RTS)
/RX: J2.11, R3.1, U3.34 (RXD0/IO3)
/SD2: U3.17 (SHD/SD2)
/SD3: U3.18 (SWP/SD3)
/SDI: J3.15, U3.22 (SDI/SD1)
/SDO: J3.14, U3.21 (SDO/SD0)
/SVN: U3.5 (SENSOR_VN)
/SVP: U3.4 (SENSOR_VP)
/TX: J2.10, U2.25 (RXD), U3.35 (TXD0/IO1)
GND: C1.2, C2.2, C3.2, C5.2, C6.2, C10.2, J2.2, J3.2, LE1.2, LE2.2, PS1.3 (-Vout), SW1.2, SW2.2, U1.1 (GND), U3.1 (GND), U3.15 (GND), U3.38 (GND), U3.39 (GND)
GNDUSB: C7.2, C8.2, C9.1, J4.A1 (GND), J4.A12 (GND), J4.B1 (GND), J4.B12 (GND), J4.S1 (SHIELD), R10.1, R11.1, U2.3 (GND), U2.29 (GND)
unnamed: C4.1, F1.1, FL1.3, RV1.2
unnamed 47: F1.2, IN1.1; also elsewhere on the board
unnamed 48: C4.2, FL1.1, IN1.2, RV1.1; also elsewhere on the board
unnamed: J4.A5 (CC1), R10.2
unnamed: J4.B5 (CC2), R11.2
unnamed: LE1.1, R1.2
unnamed: LE2.1, R2.2
unnamed: FL1.4, PS1.1 (AC/L)
unnamed: FL1.2, PS1.2 (AC/N)
unnamed: Q1.1 (B), R4.2
unnamed: Q2.2 (B), R5.2
unnamed: R7.1, SW1.1
unnamed: R9.1, SW2.1
unnamed: R3.2, U2.26 (TXD)
unnamed: C9.2, U2.6 (VDD)
VDDUSB: C7.1, C8.1, J4.A4 (VBUS), J4.A9 (VBUS), J4.B4 (VBUS), J4.B9 (VBUS), U2.7 (VREGIN), U2.8 (VBUS)

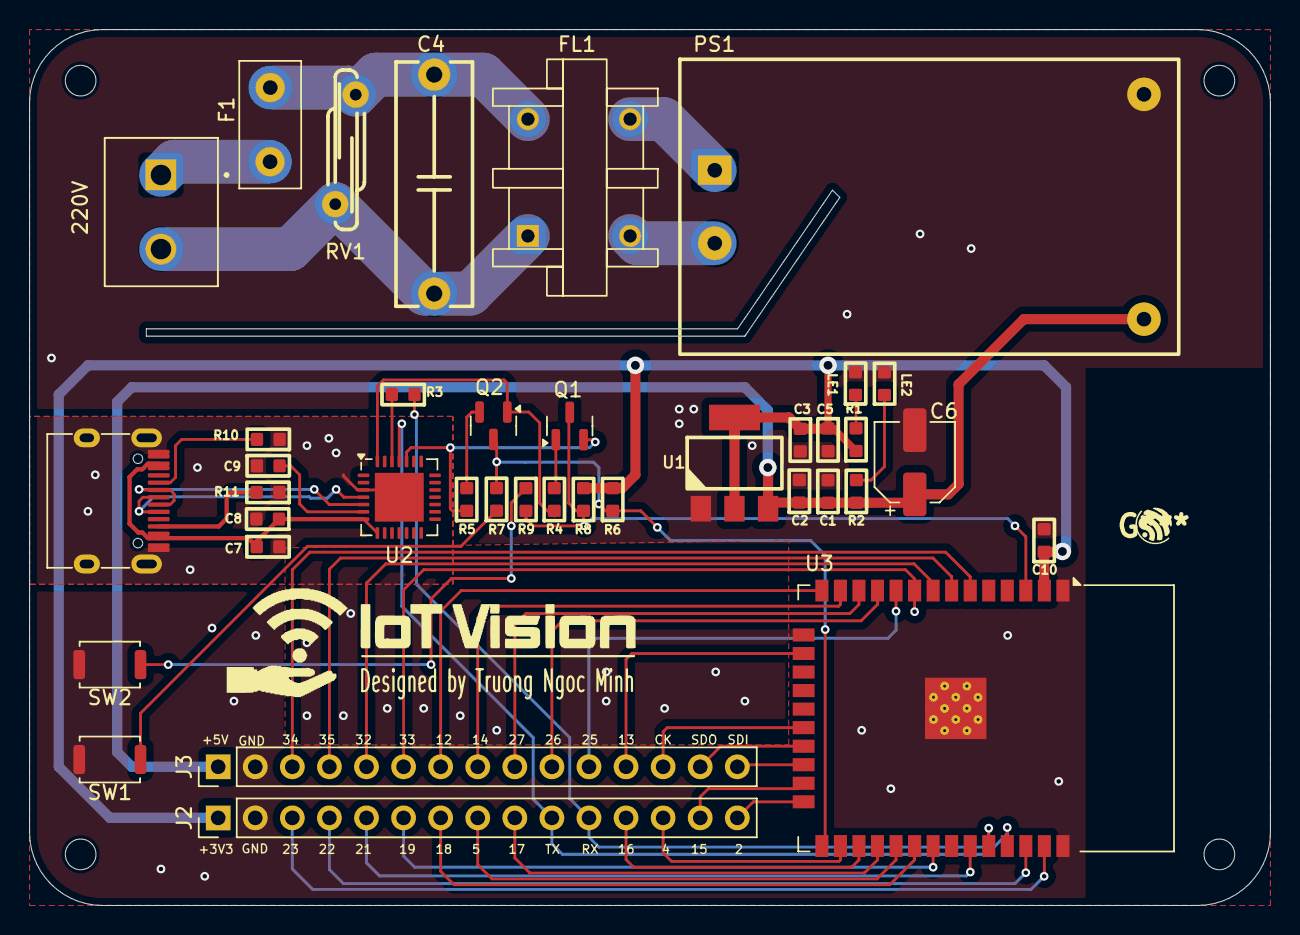
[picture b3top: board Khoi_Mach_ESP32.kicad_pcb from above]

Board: 2 copper layers, 85.0 x 60.0 mm, 38 parts (0 on the bottom side), 52 nets.

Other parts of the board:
220V: 220VAC; TerminalBlock-Vert-THT-2P-5.08mm-KF5.08

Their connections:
unnamed 47: 220V.1; also elsewhere on the board
unnamed 48: 220V.2; also elsewhere on the board

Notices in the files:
parts and their libraries:
Copyright 2021 Accelerated Designs. All rights reserved.
